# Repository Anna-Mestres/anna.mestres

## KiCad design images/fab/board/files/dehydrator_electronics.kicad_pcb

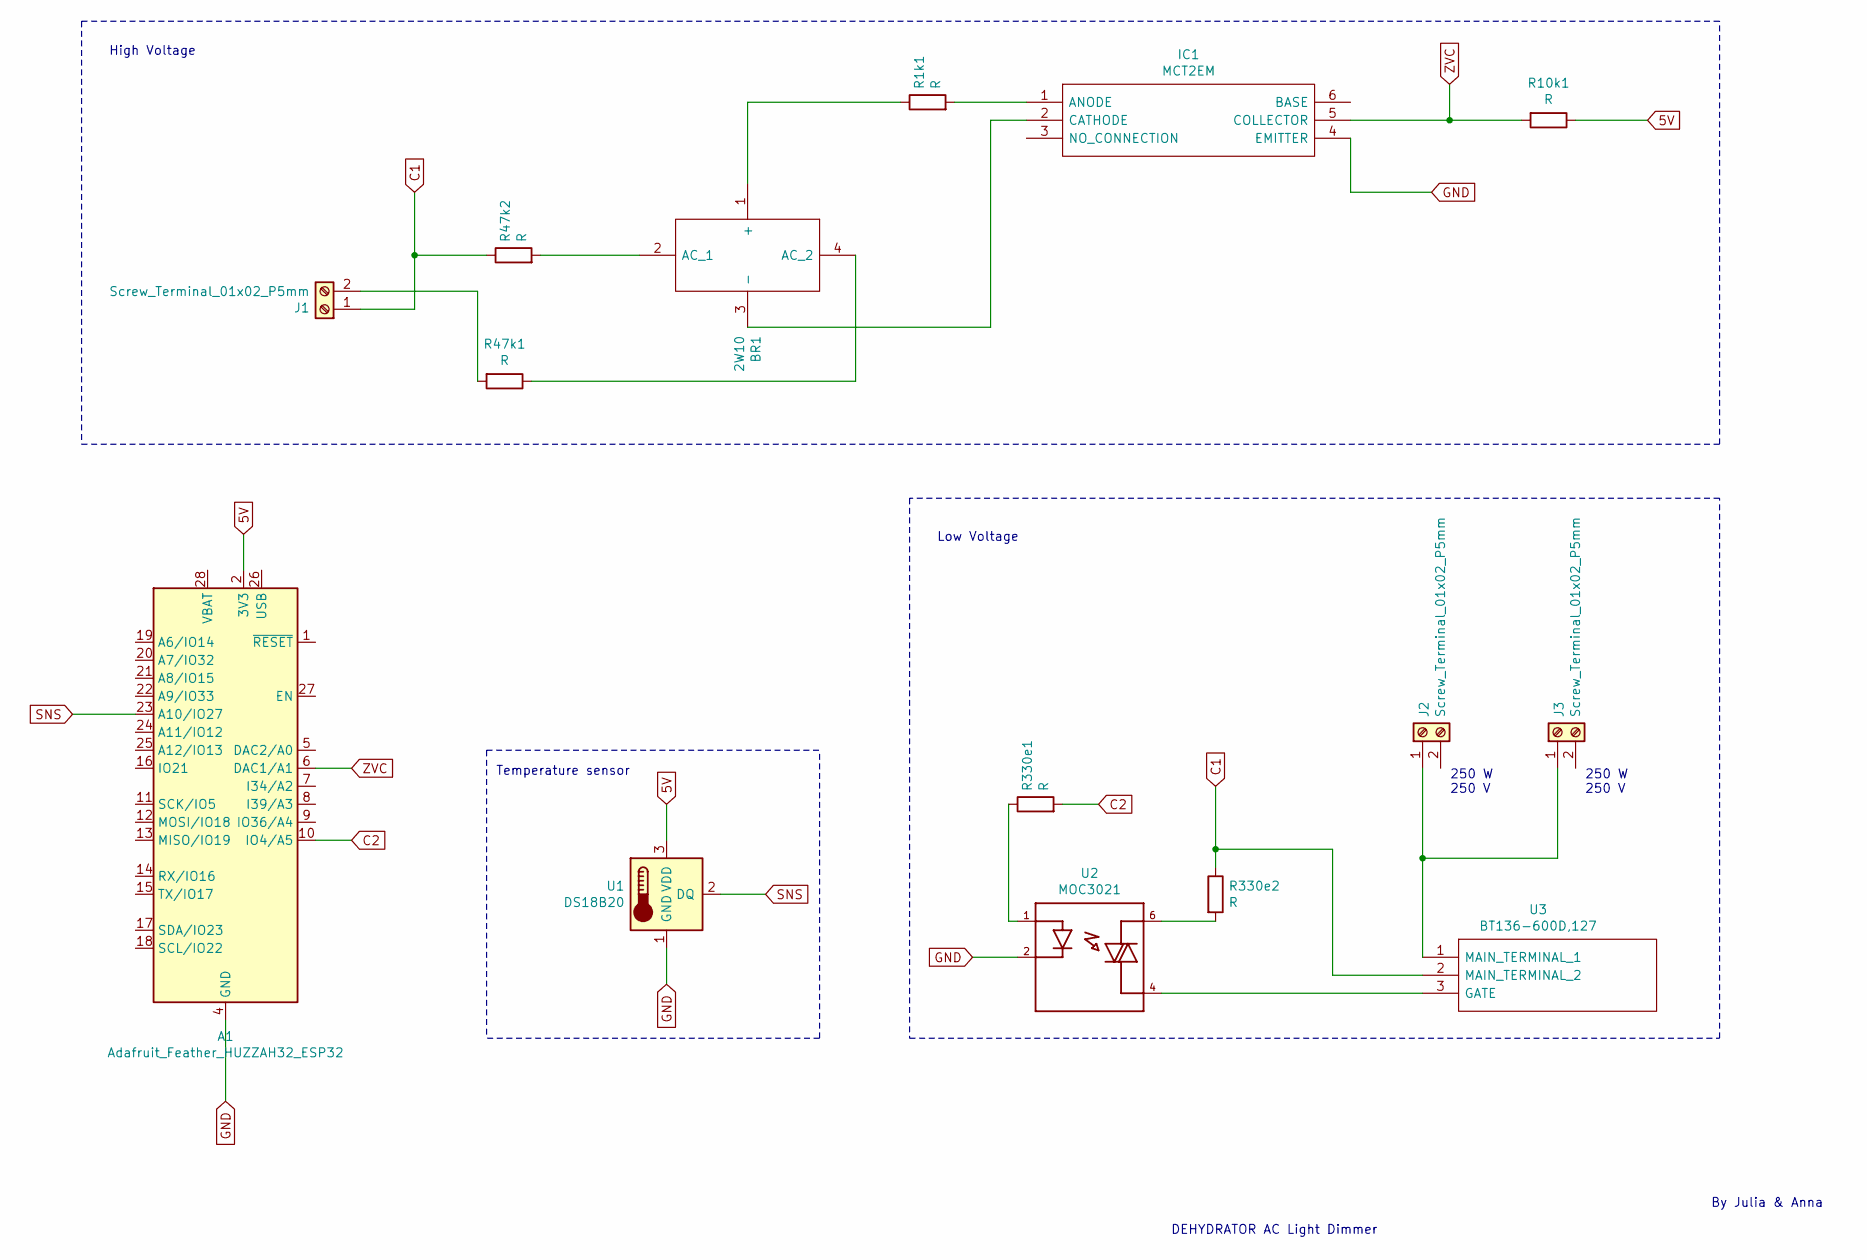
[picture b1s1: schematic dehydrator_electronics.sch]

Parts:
A1: Adafruit_Feather_HUZZAH32_ESP32; Adafruit_Feather
BR1: 2W10; Manufacturer_Part_Number 2W10
IC1: MCT2EM; DIP762W51P254L851H508Q6N; Manufacturer_Part_Number MCT2EM; Mouser Part Number 512-MCT2EM
J1, J2, J3: Screw_Terminal_01x02_P5mm; TerminalBlock_OnShore_1x02_P5.00mm_Horizontal
R1k1, R10k1, R47k1, R47k2, R330e1, R330e2: R; R_1206
U1: DS18B20; TO-92-TO92127P495H2044-3
U2: MOC3021; DIP762W45P254L889H508Q6
U3: BT136-600D,127; TO254P470X1000X2000-3P; Manufacturer_Part_Number BT136-600D,127

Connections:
5V: A1.2 (3V3), R10k1.1, U1.3 (VDD)
C1: J1.1, R47k2.1, R330e2.1, U3.2 (MAIN_TERMINAL_2)
C2: A1.10 (IO4/A5), R330e1.2
GND: A1.4 (GND), IC1.4 (EMITTER), U1.1 (GND), U2.2
unnamed: BR1.1 (+), R1k1.1
unnamed: BR1.2 (AC_1), R47k2.2
unnamed: BR1.3 (-), IC1.2 (CATHODE)
unnamed: BR1.4 (AC_2), R47k1.1
unnamed: IC1.1 (ANODE), R1k1.2
unnamed: J1.2, R47k1.2
unnamed: J2.1, J3.1, U3.1 (MAIN_TERMINAL_1)
unnamed: R330e1.1, U2.1
unnamed: R330e2.2, U2.6
unnamed: U2.4, U3.3 (GATE)
SNS: A1.23 (A10/IO27), U1.2 (DQ)
ZVC: A1.6 (DAC1/A1), IC1.5 (COLLECTOR), R10k1.2

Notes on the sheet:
250 W 250 V
DEHYDRATOR AC Light Dimmer
By Julia & Anna
High Voltage
Low Voltage
Temperature sensor

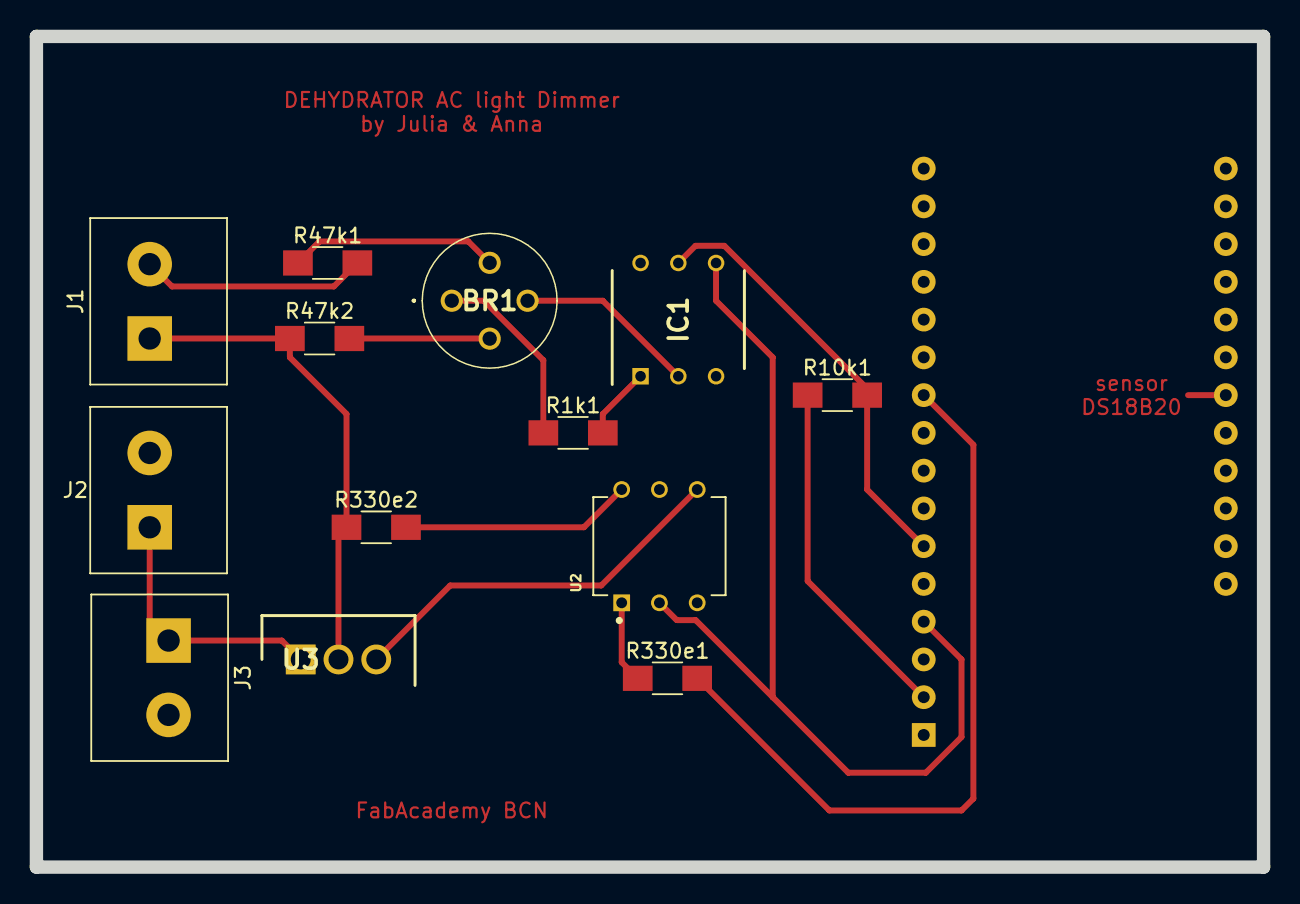
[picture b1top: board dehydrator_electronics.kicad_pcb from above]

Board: 2 copper layers, 82.5 x 55.9 mm, 14 parts (1 on the bottom side), 15 nets.

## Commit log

2021-11-03 add index
2021-11-03 add all files
2021-11-08 Add video
2021-11-08 Add photo
2021-11-08 add files
2021-11-08 add again files
2021-11-08 Add File
2021-11-12 Add Bio
2021-11-12 Add Observations
2021-11-15 Add reflections
2021-11-15 Add photos agro
2021-11-15 add photos bio
2021-11-15 Add agro file
2021-11-15 Add Bio file
2021-11-15 ADd submission file
2021-11-15 add tech beyond the myth
2021-11-17 Add Usefile
2021-11-17 Add image
2021-11-19 add submission
2021-11-19 Add tech
2021-11-19 Add Agro
2021-11-19 add images
2021-11-22 Add Video Documentation
2021-11-22 rename
2021-11-22 add comments
2021-11-23 correct sentence
2021-11-23 Upload new Collaborative Design
2021-11-24 Add map excel
2021-11-24 Add links almost useless machine
2021-11-24 add community engagement
2021-11-24 add graphs
2021-11-24 size images
2021-11-28 add map
2021-11-28 add reflection
2021-11-28 correct name file
2021-11-28 add andromines
2021-11-29 add photos
2021-12-03 add EI
2021-12-03 add EI document
2021-12-06 add commets
2021-12-06 add videos
2021-12-10 add Designing with IA
2021-12-10 change name
2021-12-10 fix errors
2021-12-13 add intervention
2021-12-13 less large file
2021-12-13 add css
2021-12-13 add size
2021-12-14 add esquema
2021-12-14 take out em
2021-12-17 ädd image
2021-12-17 add changes
2021-12-20 correct files
2021-12-28 add color
2021-12-28 add future
2021-12-28 correct some mistakes
2021-12-31 add intelligent image
2021-12-31 add errors
2022-01-03 add margin
2022-01-03 add size images
2022-01-03 correct error
2022-01-06 add agro photos
2022-01-06 change images
2022-01-06 correct errors
2022-01-08 correct erros
2022-01-08 add audio
2022-01-08 add spaces
2022-01-09 add iamges intervention
2022-01-09 add production process
2022-01-09 add explanation of the poster
2022-01-11 add reports in html
2022-01-11 add Hug me Not
2022-01-11 add presentation
2022-01-11 add presentation pdf
2022-01-13 add billion
2022-01-13 add document
2022-01-14 add wakanda work
2022-01-24 add kick off
2022-01-24 add design space pdf
2022-01-28 add fab acadamy
2022-01-28 add pages
2022-01-28 add challenges
2022-01-30 add weekly report
2022-01-30 trying to fix errror
2022-01-30 add graphic
2022-02-06 add document remixing materials
2022-02-06 add process picture
2022-02-06 add submission lara
2022-02-09 add w2
2022-02-13 add gif
2022-02-13 add gif2
2022-02-18 add challenge 1
2022-02-19 add more detail
2022-02-19 add files week 3
2022-02-20 add new files
2022-02-21 images remixing materials I final
2022-02-21 add reflection laura
2022-02-22 add images intervention 3
2022-03-01 add brand reflection
2022-03-01 add w5
2022-03-02 add images w5
2022-03-08 add board files
2022-03-08 add iamges
2022-03-08 add esquemas
2022-03-08 add w6
2022-03-10 add explanation
2022-03-16 add abstract
2022-03-16 correct mistakes abstract
2022-03-20 add atlas of weak signals
2022-03-21 add reflections questions
2022-03-22 add w8 fabacademy
2022-03-22 change aesthetics
2022-04-03 add text
2022-04-16 add writing
2022-04-16 correct name
2022-04-21 add design studio
2022-04-21 add 4 intervention
2022-04-21 add last reflection
2022-04-21 add designspace
2022-04-21 add design space
2022-04-26 add cnc gif
2022-04-26 add cnc gif2
2022-04-26 add photos cnc
2022-04-26 add cnc
2022-04-27 add w9 and w11/13
2022-04-27 add and remove images
2022-04-27 add gif placa
2022-04-27 add files proces
2022-04-27 add gif c2
2022-04-27 add c2
2022-05-09 add w4
2022-05-11 add output w13
2022-05-28 add w9, w17 and w18
2022-05-28 add images mold
2022-05-28 add gif llums
2022-05-28 add images w17-18
2022-05-30 add final images molding
2022-05-30 add images molding
2022-05-30 add term3
2022-05-30 add design study 3
2022-06-03 add challenge 4
2022-06-03 add challenge3
2022-06-06 add kick3
2022-06-06 add alternative presents
2022-06-07 add w14 and w15
2022-06-07 add w14 and 15
2022-06-07 change name pictures
2022-06-07 add images toys and family
2022-06-07 add images fam
2022-06-07 add images toys
2022-06-07 add intervention 4
2022-06-08 add iamges w16
2022-06-08 add w16
2022-06-10 add file mallorca
2022-06-10 add mallorca trip
2022-06-11 reduce size pdf
2022-06-11 add collective
2022-06-11 add scalability and interventions
2022-06-11 add the field
2022-06-13 add proces juguem
2022-06-13 add screenshots
2022-06-14 add manifesto
2022-06-14 add images juguem
2022-06-15 add last changes
2022-06-17 add final reflection
